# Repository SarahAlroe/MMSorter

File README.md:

# MMSorter
M&amp;M's sorter - The unnecessarily hard way

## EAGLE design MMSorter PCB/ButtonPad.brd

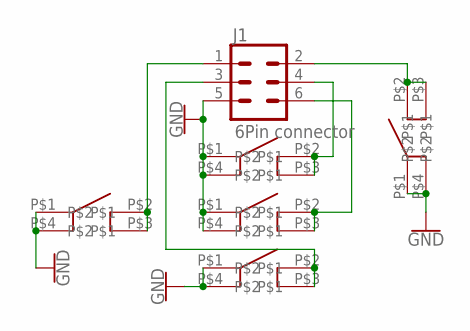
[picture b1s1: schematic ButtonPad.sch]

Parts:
J1: 6Pin connector; 2X3
U$1, U$2, U$3, U$4, U$5: BUTTON_GRAY_12MM; BUTTON_12MM

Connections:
GND: J1.5, U$1.P$1, U$1.P$4, U$2.P$1, U$2.P$4, U$3.P$1, U$3.P$4, U$4.P$1, U$4.P$4, U$5.P$1, U$5.P$4
unnamed: J1.1, U$5.P$2, U$5.P$3
unnamed: J1.3, U$3.P$2, U$3.P$3
unnamed: J1.6, U$2.P$2, U$2.P$3
unnamed: J1.4, U$1.P$2, U$1.P$3
unnamed: J1.2, U$4.P$2, U$4.P$3

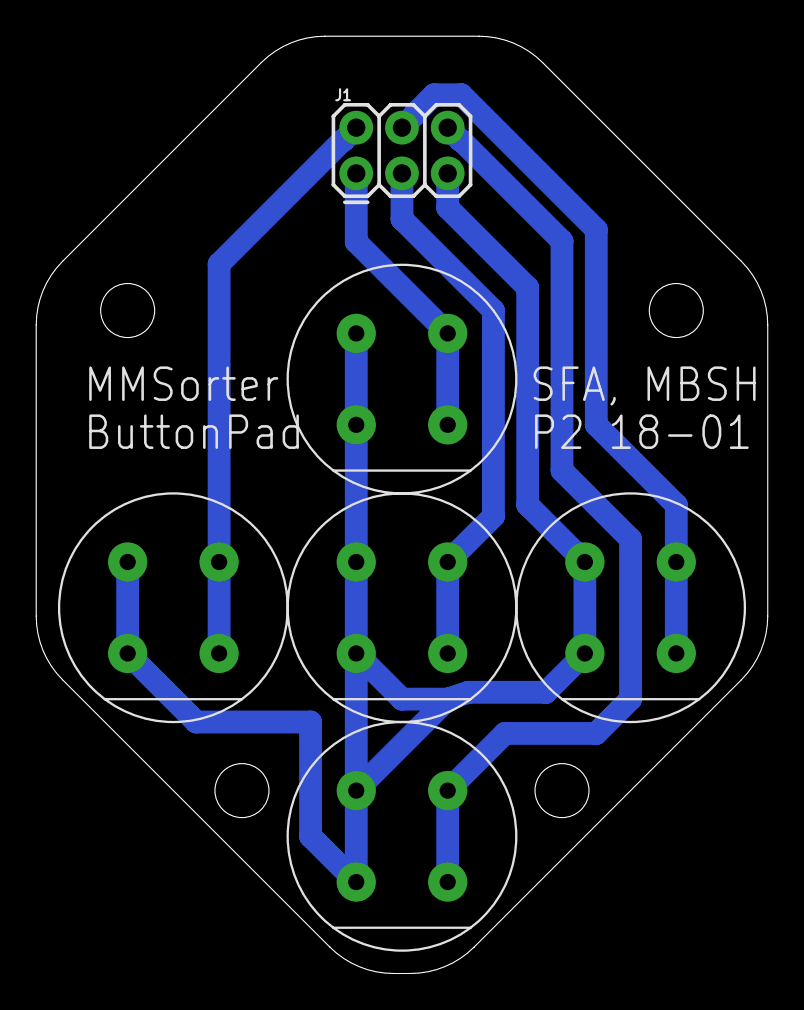
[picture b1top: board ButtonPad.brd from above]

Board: 2 copper layers, 40.6 x 52.1 mm, 6 parts (0 on the bottom side), 6 nets.

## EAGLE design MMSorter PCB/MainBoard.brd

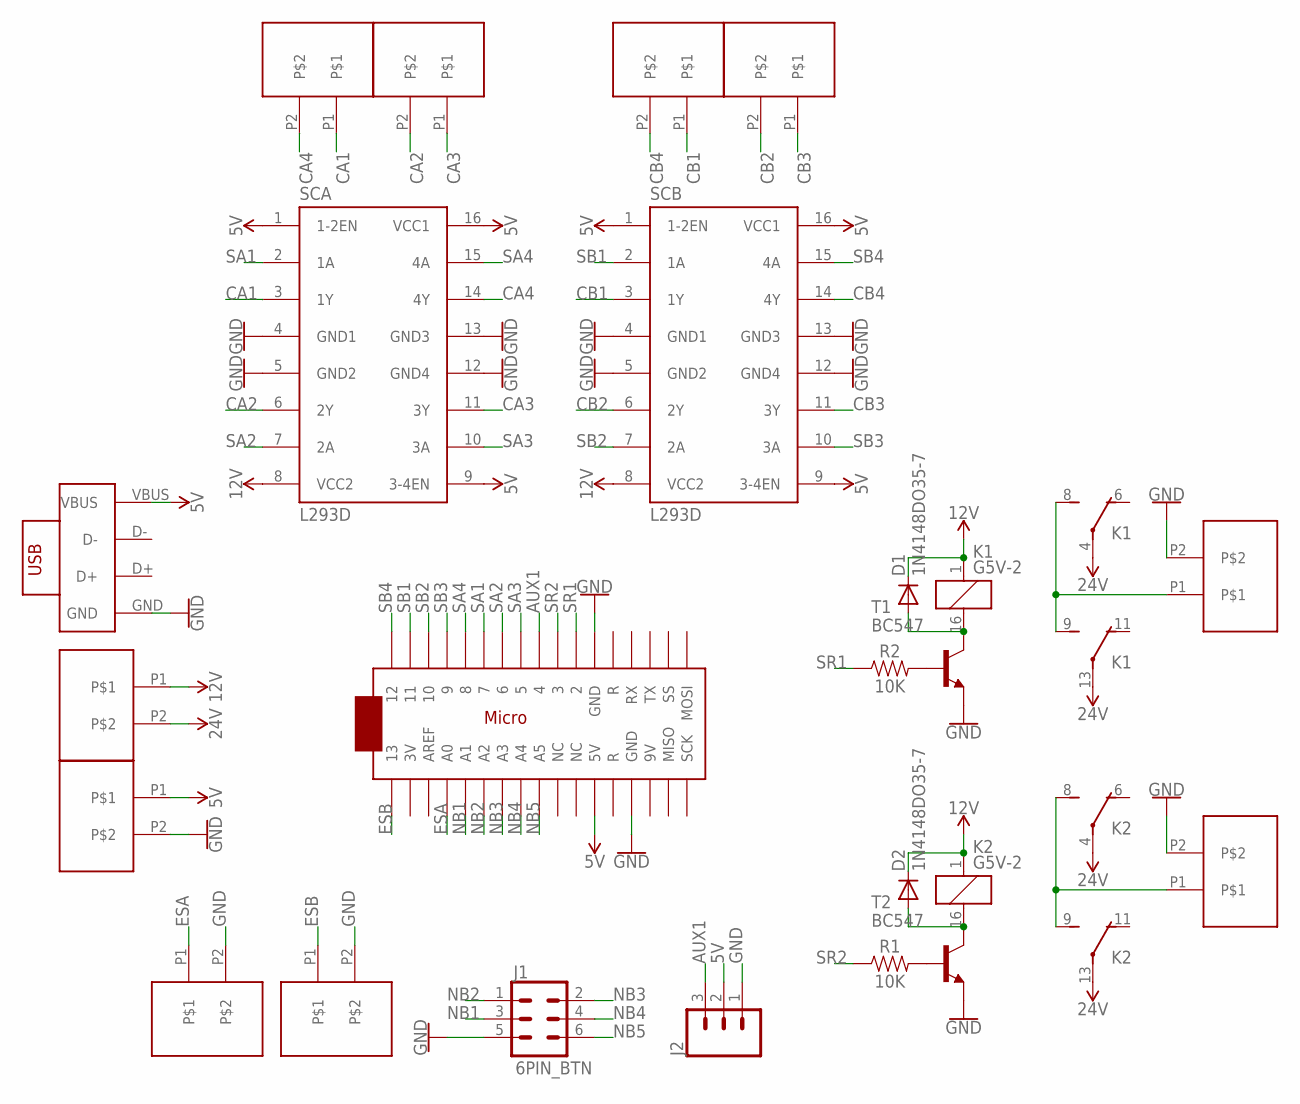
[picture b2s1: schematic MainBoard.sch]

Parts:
5V/GND, 12/24V: PRT-08432
D1, D2: 1N4148DO35-7; DO35-7
ESA: PRT-08432
ESB: PRT-08432
J1: 6PIN_BTN; 2X3
J2: CONN_03; 1X03
K1, K2: G5V-2
R1, R2: 10K; AXIAL-0.3
SCA: L293D; DIL16
SCA12, SCA34: PRT-08432
SCB: L293D; DIL16
SCB12, SCB34: PRT-08432
SR1, SR2: PRT-08432
T1, T2: BC547; TO92
U$1: ARDUINOMICRO
U$2: USB_EXP_BOARD; USB_EXPANSION

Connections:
5V: 5V/GND.P1, J2.2, SCA.1 (1-2EN), SCA.9 (3-4EN), SCA.16 (VCC1), SCB.1 (1-2EN), SCB.9 (3-4EN), SCB.16 (VCC1), U$1.P$23 (5V), U$2.VBUS
12V: 12/24V.P1, D1.C, D2.C, K1.1, K2.1, SCA.8 (VCC2), SCB.8 (VCC2)
AUX1: J2.3, U$1.P$9 (4)
CA1: SCA.3 (1Y), SCA12.P1
CA2: SCA.6 (2Y), SCA34.P2
CA3: SCA.11 (3Y), SCA34.P1
CA4: SCA.14 (4Y), SCA12.P2
CB1: SCB.3 (1Y), SCB12.P1
CB2: SCB.6 (2Y), SCB34.P2
CB3: SCB.11 (3Y), SCB34.P1
CB4: SCB.14 (4Y), SCB12.P2
ESA: ESA.P1, U$1.P$31 (A0)
ESB: ESB.P1, U$1.P$34 (13)
GND: 5V/GND.P2, ESA.P2, ESB.P2, J1.5, J2.1, SCA.4 (GND1), SCA.5 (GND2), SCA.12 (GND4), SCA.13 (GND3), SCB.4 (GND1), SCB.5 (GND2), SCB.12 (GND4), SCB.13 (GND3), SR1.P2, SR2.P2, T1.1 (E), T2.1 (E), U$1.P$12 (GND), U$1.P$21 (GND), U$2.GND
unnamed: D2.A, K2.16 (2), T2.3 (C)
unnamed: D1.A, K1.16 (2), T1.3 (C)
unnamed: R1.P$2 (2), T2.2 (B)
unnamed: R2.P$2 (2), T1.2 (B)
NB1: J1.3, U$1.P$30 (A1)
NB2: J1.1, U$1.P$29 (A2)
NB3: J1.2, U$1.P$28 (A3)
NB4: J1.4, U$1.P$27 (A4)
NB5: J1.6, U$1.P$26 (A5)
RT1: K1.8 (S), K1.9 (S), SR1.P1
RT2: K2.8 (S), K2.9 (S), SR2.P1
SA1: SCA.2 (1A), U$1.P$6 (7)
SA2: SCA.7 (2A), U$1.P$7 (6)
SA3: SCA.10 (3A), U$1.P$8 (5)
SA4: SCA.15 (4A), U$1.P$5 (8)
SB1: SCB.2 (1A), U$1.P$2 (11)
SB2: SCB.7 (2A), U$1.P$3 (10)
SB3: SCB.10 (3A), U$1.P$4 (9)
SB4: SCB.15 (4A), U$1.P$1 (12)
SR1: R2.P$1 (1), U$1.P$11 (2)
SR2: R1.P$1 (1), U$1.P$10 (3)
VCC: 12/24V.P2, K1.4, K1.13, K2.4, K2.13

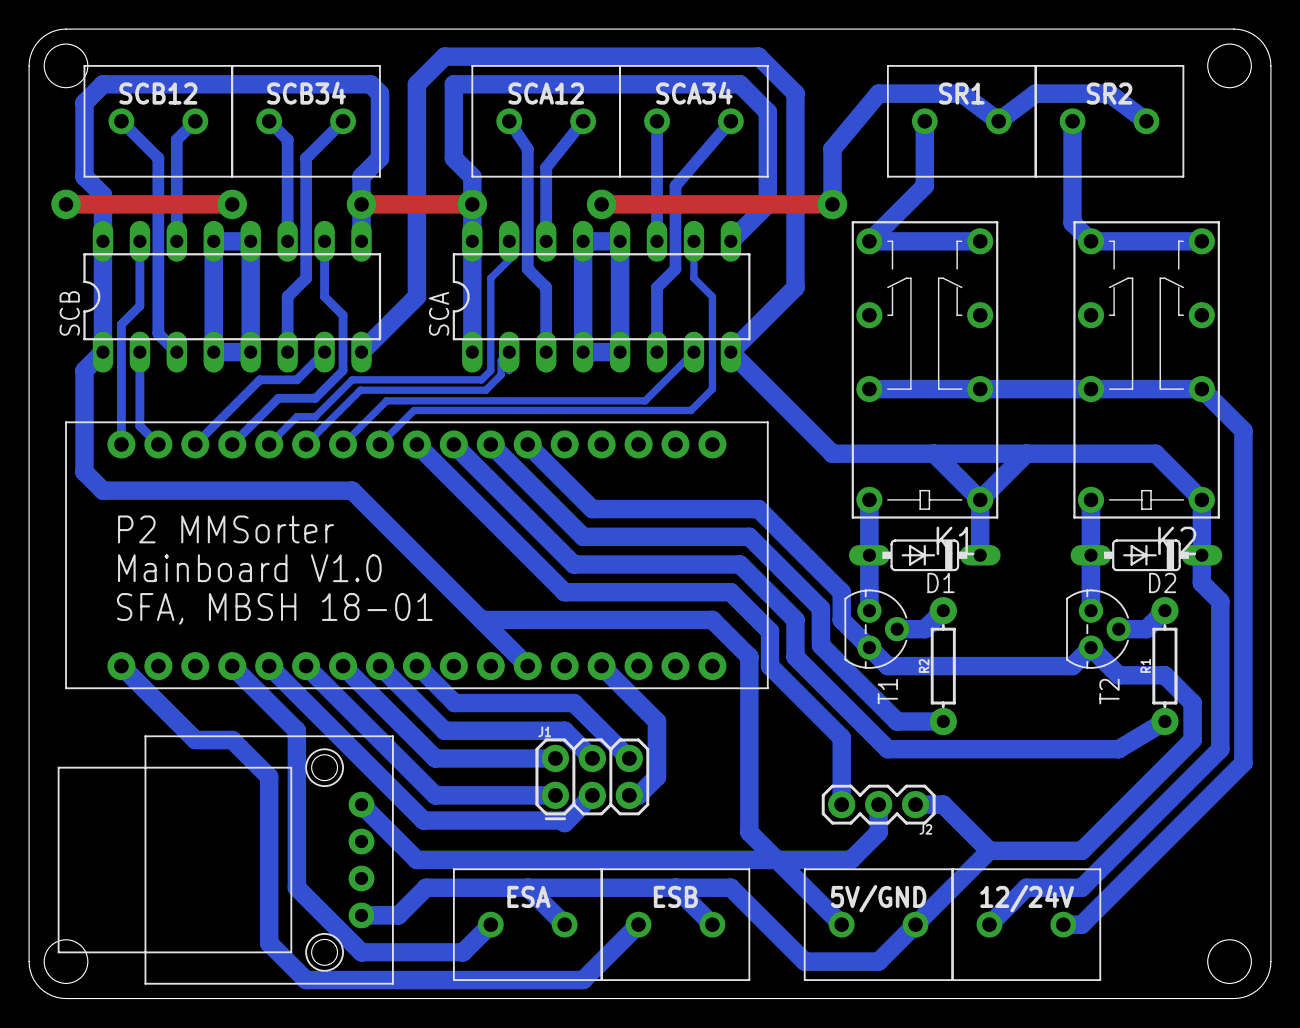
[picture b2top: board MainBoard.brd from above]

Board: 2 copper layers, 85.4 x 66.7 mm, 24 parts (0 on the bottom side), 36 nets.

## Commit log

2018-01-25 init
2018-01-26 General progress
2018-01-29 Arduino stuff should be working now
2018-01-29 Added Eagle PCBs
2018-01-30 Added inventor drawings
    Parts and assemblies
2018-01-31 Fixed stupid mistakes
2018-02-01 Fixed dumb const progmeme
2018-02-01 More general progress
2018-02-01 Made. it. work.
2018-02-08 Added picamera picture stuff
2018-02-08 Possible camera error fix
2018-02-08 Partial revert. Just testing
2018-02-08 General improvements
2018-02-11 Added new test image
2018-02-11 Added color calibration

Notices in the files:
parts and their libraries:
SparkFun-Connectors: Licensing: Creative Commons ShareAlike 4.0 International - https://creativecommons.org/licenses/by-sa/4.0
